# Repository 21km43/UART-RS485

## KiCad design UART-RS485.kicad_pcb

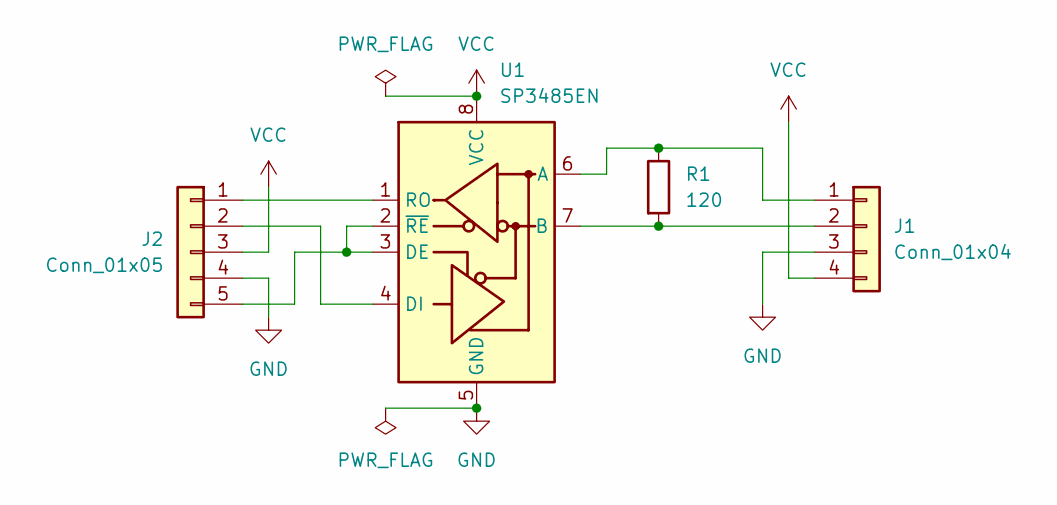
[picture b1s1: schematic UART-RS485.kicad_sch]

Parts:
J1: Conn_01x04; JST_XH_S4B-XH-A_1x04_P2.50mm_Horizontal
J2: Conn_01x05; JST_XH_S5B-XH-A_1x05_P2.50mm_Horizontal
R1: 120; R_0805_2012Metric; LCSC C17437
U1: SP3485EN; SOIC-8_3.9x4.9mm_P1.27mm; LCSC C8963

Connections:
GND: J1.3, J2.4, U1.5 (GND)
unnamed: J1.1, R1.1, U1.6 (A)
unnamed: J1.2, R1.2, U1.7 (B)
unnamed: J2.1, U1.1 (RO)
unnamed: J2.2, U1.4 (DI)
unnamed: J2.5, U1.2 (~RE), U1.3 (DE)
VCC: J1.4, J2.3, U1.8 (VCC)

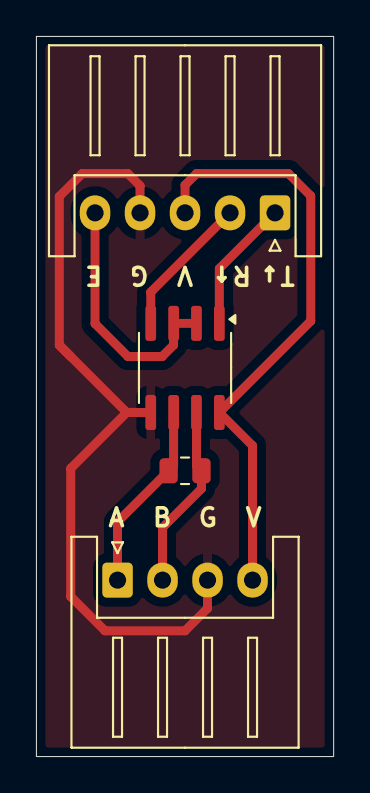
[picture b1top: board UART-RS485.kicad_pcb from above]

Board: 2 copper layers, 16.5 x 40.0 mm, 4 parts (0 on the bottom side), 7 nets.

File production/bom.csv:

Designator,Footprint,Quantity,Value,LCSC Part #
J1,JST_XH_S4B-XH-A_1x04_P2.50mm_Horizontal,1,Conn_01x04,
J2,JST_XH_S5B-XH-A_1x05_P2.50mm_Horizontal,1,Conn_01x05,
R1,0805,1,120,C17437
U1,SOIC-8_3.9x4.9mm_P1.27mm,1,SP3485EN,C8963

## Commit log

2025-03-25 add tx rx arrow
